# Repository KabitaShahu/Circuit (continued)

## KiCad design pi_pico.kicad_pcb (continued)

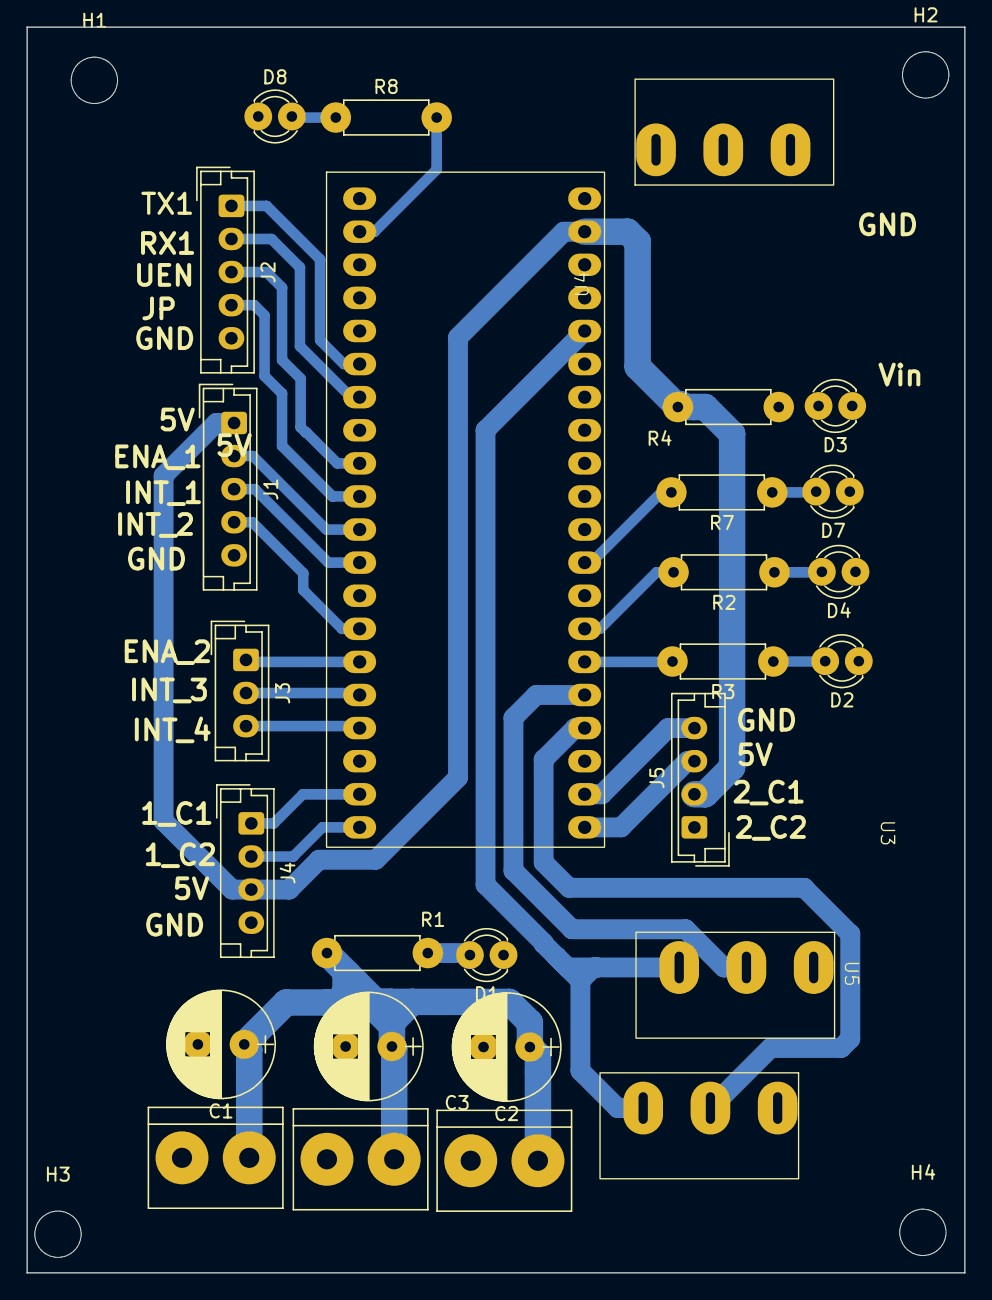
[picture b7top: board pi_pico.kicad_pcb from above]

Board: 2 copper layers, 70.8 x 94.1 mm, 31 parts (0 on the bottom side), 28 nets.

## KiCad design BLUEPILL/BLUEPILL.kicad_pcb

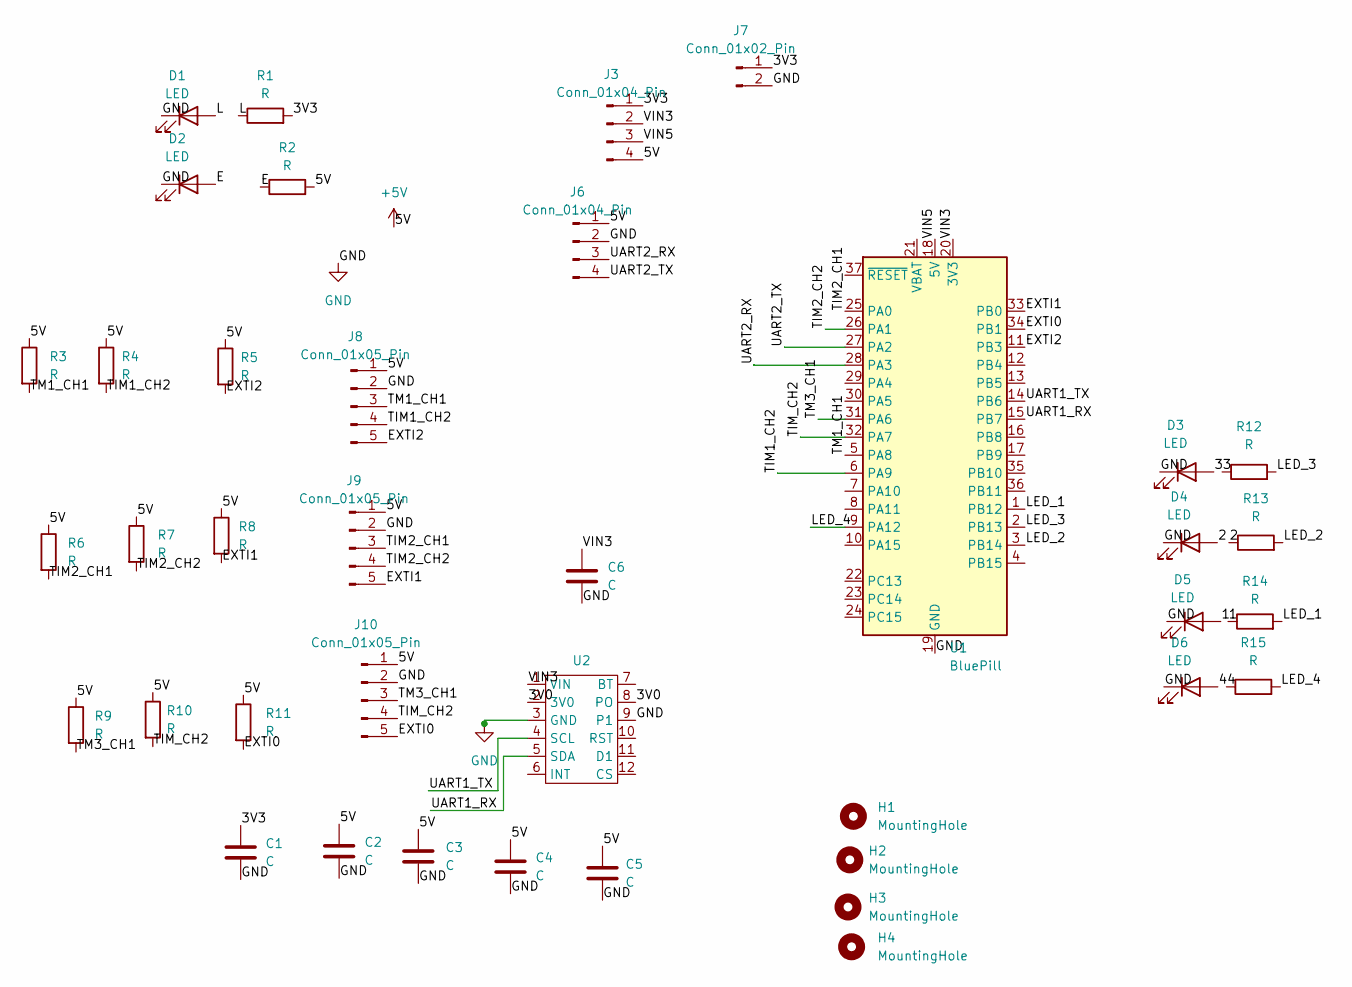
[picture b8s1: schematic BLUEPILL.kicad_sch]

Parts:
C1: C; Capacitor_10uF
C2: C; Capacitor_100uF
C3, C4, C5, C6: C; Capacitor_Disc_Small
D1, D2, D3, D4, D5, D6: LED; LED_D3.0mm
H1, H2, H3, H4: MountingHole; MountingHole_3.2mm_M3
J3: Conn_01x04_Pin; PinHeader_1x04_P2.54mm_Vertical
J6: Conn_01x04_Pin; jst_4
J7: Conn_01x02_Pin; JST_EH_B2B-EH-A_1x02_P2.50mm_Vertical
J8, J9, J10: Conn_01x05_Pin; JST_EH_B5B-EH-A_1x05_P2.50mm_Vertical
R1, R2, R3, R4, R5, R6, R7, R8, R9, R10, R11, R12, R13, R14, R15: R; Resistor_small
U1: BluePill; STM32_BLUEPLL_MOD
U2: bno08

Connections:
+5V: C2.1, C3.1, C4.1, C5.1, J3.4, J6.1, J8.1, J9.1, J10.1, R2.2, R3.1, R4.1, R5.1, R6.1, R7.1, R8.1, R9.1, R10.1, R11.1
/1: D5.2 (A), R14.1
/2: D4.2 (A), R13.1
/3: D3.2 (A), R12.1
/3V0: U2.2 (3V0), U2.8 (PO)
/3V3: C1.1, J3.1, J7.1, R1.2
/4: D6.2 (A), R15.1
/E: D2.2 (A), R2.1
/EXTI0: J10.5, R11.2, U1.34 (PB1)
/EXTI1: J9.5, R8.2, U1.33 (PB0)
/EXTI2: J8.5, R5.2, U1.11 (PB3)
/L: D1.2 (A), R1.1
/LED_1: R14.2, U1.1 (PB12)
/LED_2: R13.2, U1.3 (PB14)
/LED_3: R12.2, U1.2 (PB13)
/LED_4: R15.2, U1.9 (PA12)
/TIM1_CH2: J8.4, R4.2, U1.6 (PA9)
/TIM2_CH1: J9.3, R6.2, U1.25 (PA0)
/TIM2_CH2: J9.4, R7.2, U1.26 (PA1)
/TIM_CH2: J10.4, R10.2, U1.32 (PA7)
/TM1_CH1: J8.3, R3.2, U1.5 (PA8)
/TM3_CH1: J10.3, R9.2, U1.31 (PA6)
/UART1_RX: U1.15 (PB7), U2.5 (SDA)
/UART1_TX: U1.14 (PB6), U2.4 (SCL)
/UART2_RX: J6.3, U1.28 (PA3)
/UART2_TX: J6.4, U1.27 (PA2)
/VIN3: C6.1, J3.2, U1.20 (3V3), U1.38 (3V3), U2.1 (VIN)
/VIN5: J3.3, U1.18 (5V)
GND: C1.2, C2.2, C3.2, C4.2, C5.2, C6.2, D1.1 (K), D2.1 (K), D3.1 (K), D4.1 (K), D5.1 (K), D6.1 (K), J6.2, J7.2, J8.2, J9.2, J10.2, U1.19 (GND), U1.39 (GND), U1.40 (GND), U2.3 (GND), U2.9 (P1)

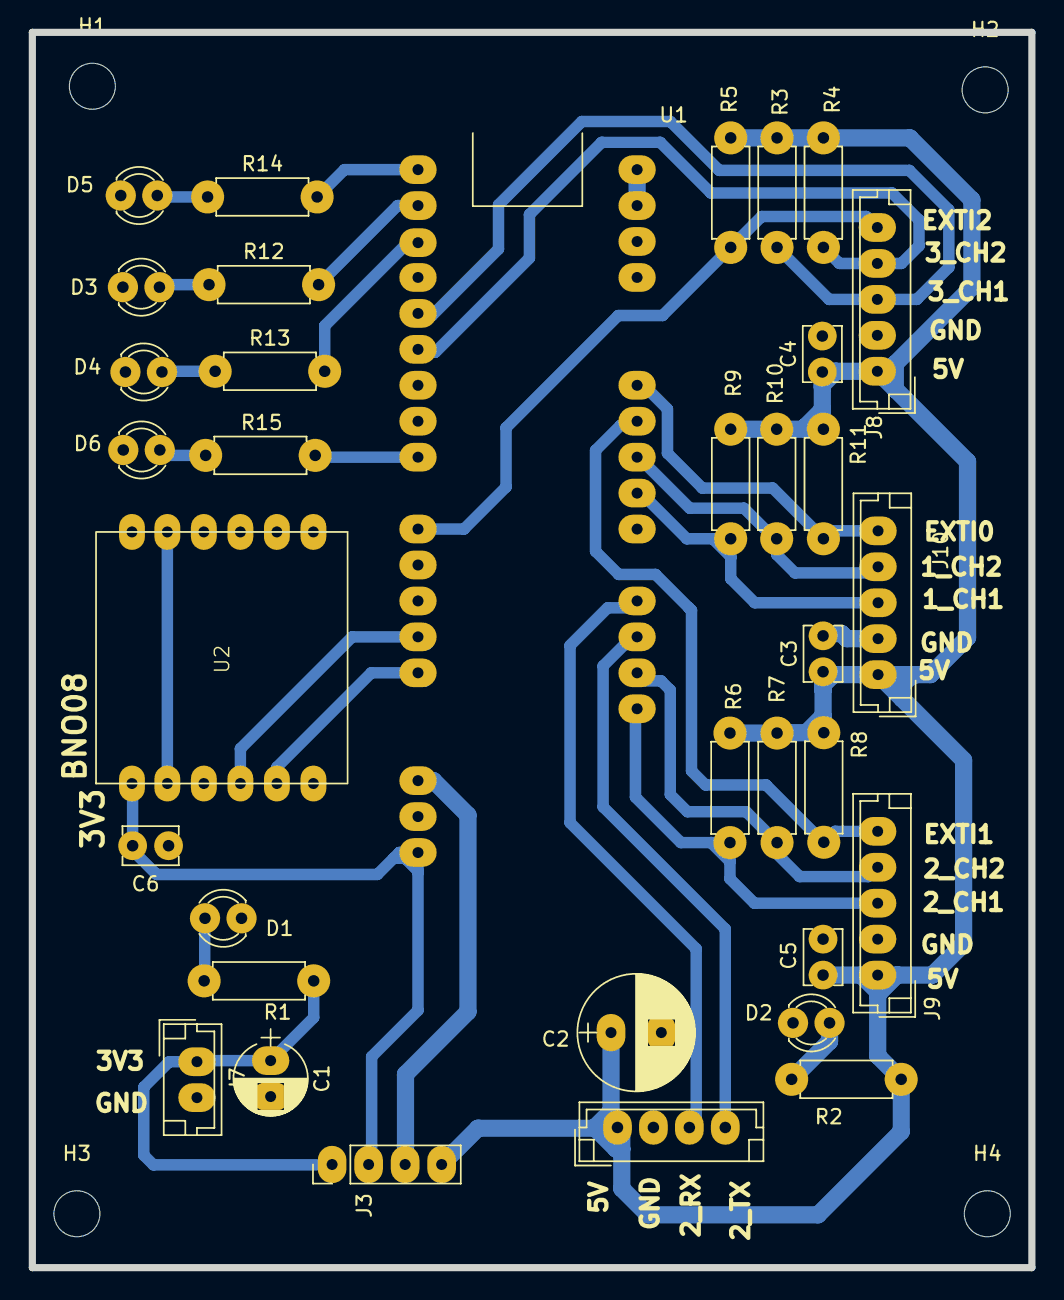
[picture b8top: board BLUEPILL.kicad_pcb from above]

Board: 2 copper layers, 69.5 x 85.9 mm, 39 parts (0 on the bottom side), 29 nets.
